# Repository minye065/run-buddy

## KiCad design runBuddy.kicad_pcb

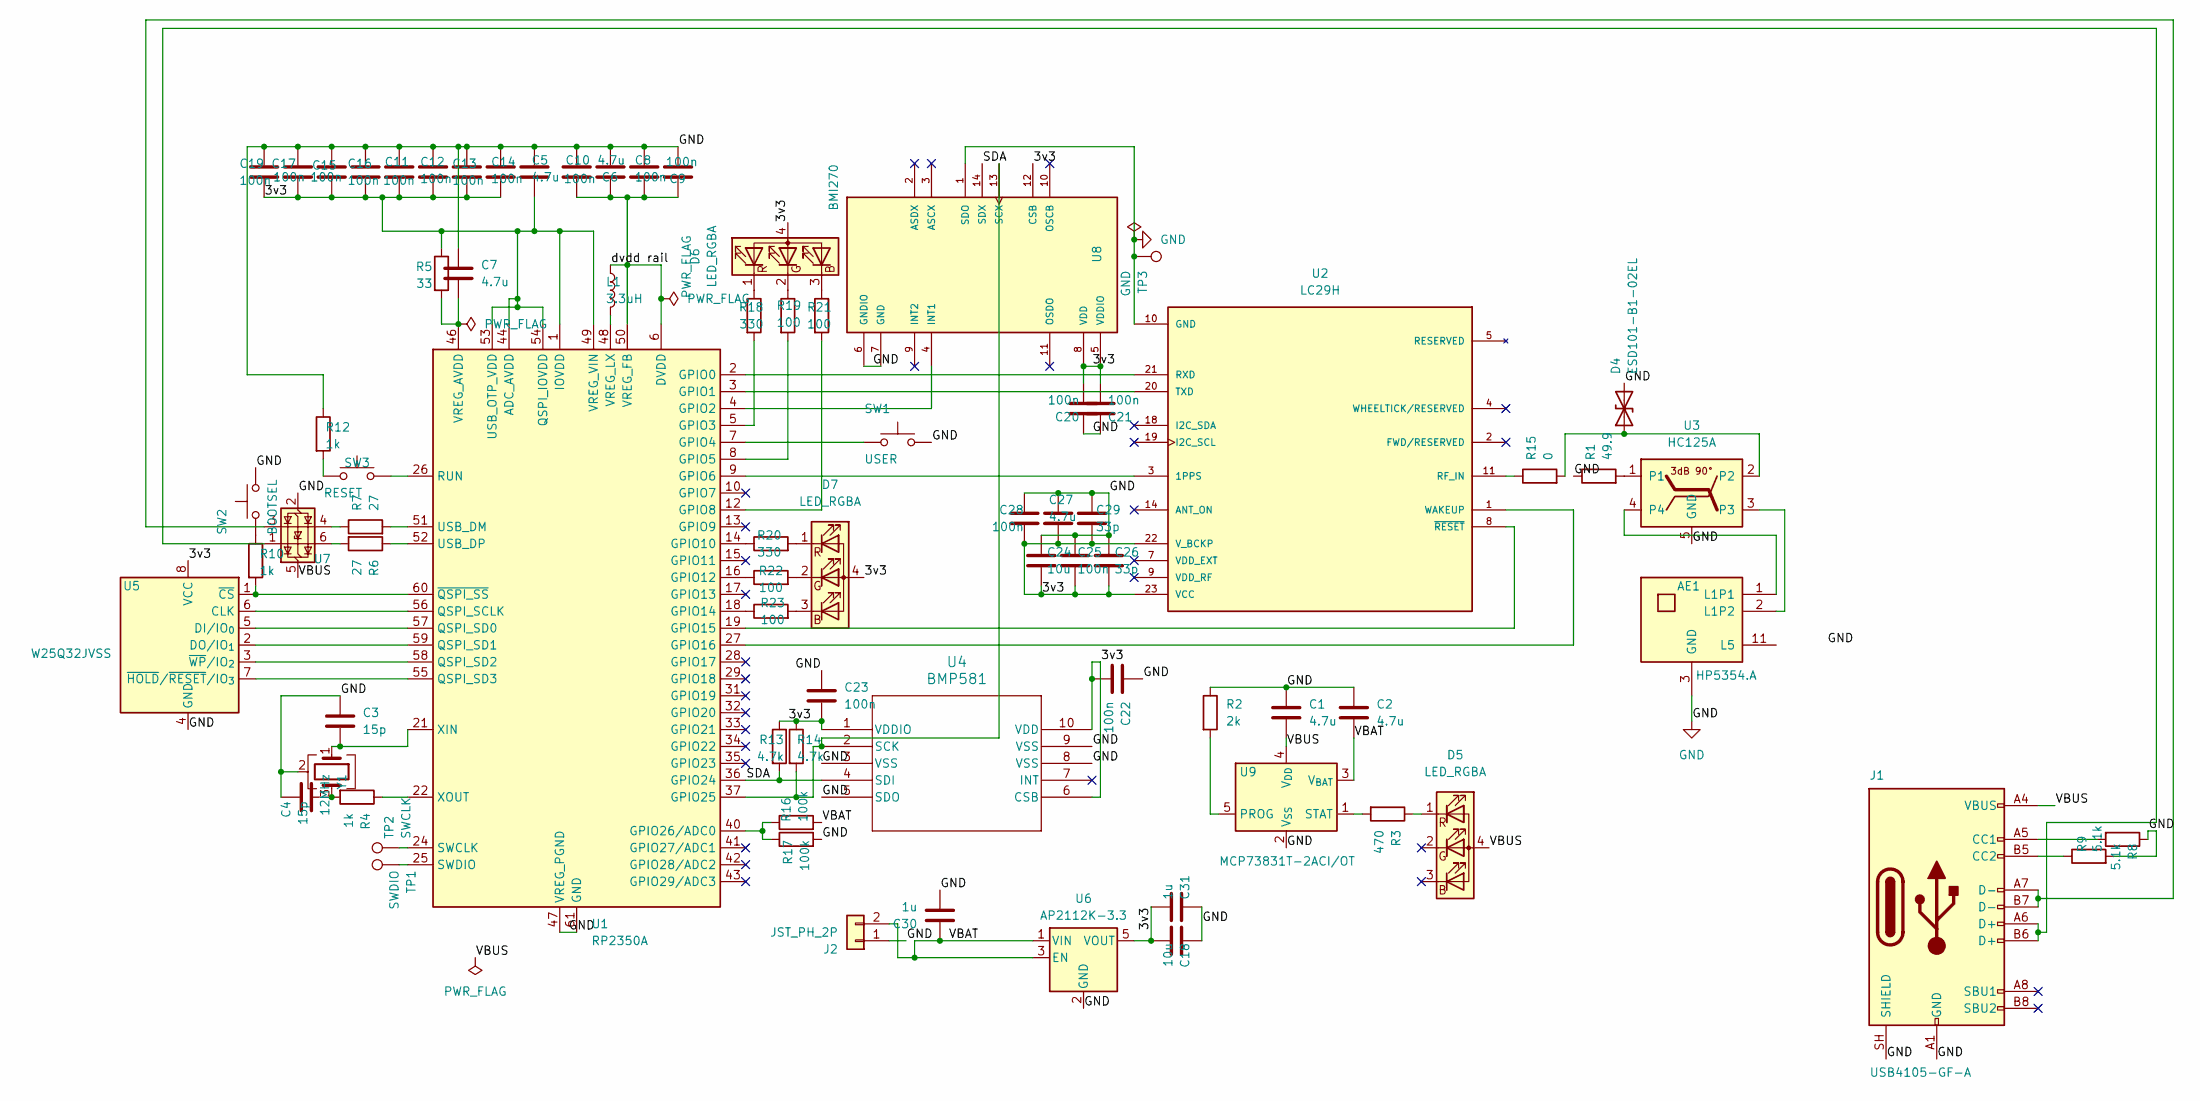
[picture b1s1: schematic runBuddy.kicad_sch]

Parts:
AE1: HP5354.A; MPN HP5354.A
C1, C2, C5, C6, C7, C27: 4.7u; C_0402_1005Metric
C3, C4: 15p; C_0402_1005Metric
C8, C9, C10, C11, C12, C13, C14, C15, C16, C17, C19, C20, C21, C22, C23, C25, C28: 100n; C_0402_1005Metric
C18: 10u; C_0805_2012Metric
C24: 10u; C_0402_1005Metric
C26, C29: 33p; C_0402_1005Metric
C30, C31: 1u; C_0402_1005Metric
D4: ESD101-B1-02EL; D_0201_0603Metric; MPN ESD101-B1-02EL
D5, D6, D7: LED_RGBA; 150066M153000
J1: USB4105-GF-A; USB_C_Receptacle_GCT_USB4105-xx-A_16P_TopMnt_Horizontal; MPN USB4105-GF-A
J2: JST_PH_2P; JST_PH_B2B-PH-K_1x02_P2.00mm_Vertical
L1: 3.3uH; AOTA-B2016; MPN AOTA-B201610S3R3-101-T
R1: 49.9; R_0402_1005Metric; MPN ERJ-2RKF49R9X
R2: 2k; R_0402_1005Metric
R3: 470; R_0402_1005Metric
R4, R10, R12: 1k; R_0402_1005Metric
R5: 33; R_0402_1005Metric
R6, R7: 27; R_0402_1005Metric
R8, R9: 5.1k; R_0402_1005Metric
R13, R14: 4.7k; R_0402_1005Metric
R15: 0; R_0402_1005Metric
R16, R17: 100k; R_0402_1005Metric
R18, R20: 330; R_0402_1005Metric
R19, R21, R22, R23: 100; R_0402_1005Metric
SW1: USER; SW_Push_1P1T_NO_Vertical_Wuerth_434133025816; MPN 434133025816
SW2: BOOTSEL; SW_Push_1P1T_NO_Vertical_Wuerth_434133025816; MPN 434133025816
SW3: RESET; SW_Push_1P1T_NO_Vertical_Wuerth_434133025816; MPN 434133025816
TP1: SWDIO; TestPoint_Pad_D1.0mm
TP2: SWCLK; TestPoint_Pad_D1.0mm
TP3: GND; TestPoint_Pad_D1.0mm
U1: RP2350A; QFN-60-1EP_7x7mm_P0.4mm_EP3.4x3.4mm
U2: LC29H; PARTREV 1.1
U3: HC125A; MPN HC125A
U4: BMP581
U5: W25Q32JVSS; SOIC-8_5.3x5.3mm_P1.27mm
U6: AP2112K-3.3; SOT-23-5
U7: USBLC6-2SC6; SOT-23-6
U8: BMI270
U9: MCP73831T-2ACI/OT; SOT-23-5; MPN MCP73831T-2ACI/OT
Y1: 12MHz; Crystal_SMD_3225-4Pin_3.2x2.5mm; MPN ABM8-272-T3

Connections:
/3v3: C5.2, C11.2, C12.2, C13.2, C14.2, C15.2, C16.2, C17.2, C18.2, C19.2, C20.2, C21.2, C22.2, C23.2, C24.2, C25.2, C26.2, C27.2, C28.2, C29.2, C31.2, D6.4 (A), D7.4 (A), R5.1, R13.1, R14.1, U1.1 (IOVDD), U1.11 (IOVDD), U1.20 (IOVDD), U1.30 (IOVDD), U1.38 (IOVDD), U1.44 (ADC_AVDD), U1.45 (IOVDD), U1.49 (VREG_VIN), U1.53 (USB_OTP_VDD), U1.54 (QSPI_IOVDD), U2.22 (V_BCKP), U2.23 (VCC), U4.1 (VDDIO), U4.6 (CSB), U4.10 (VDD), U5.8 (VCC), U6.5 (VOUT), U8.5 (VDDIO), U8.8 (VDD), U8.12 (CSB)
/SDA: R13.2, U1.36 (GPIO24), U4.4 (SDI), U8.14 (SDX)
/VBAT: C2.2, C30.1, J2.2, R16.2, U6.1 (VIN), U6.3 (EN), U9.3 (V_{BAT})
/VBUS: C1.2, D5.4 (A), J1.A4 (VBUS), J1.A9 (VBUS), J1.B4 (VBUS), J1.B9 (VBUS), U7.5 (VBUS), U9.4 (V_{DD})
/dvdd rail: C6.2, C8.2, C9.1, C10.2, L1.1, U1.6 (DVDD), U1.23 (DVDD), U1.39 (DVDD), U1.50 (VREG_FB)
GND: AE1.3 (GND), AE1.4 (GND), AE1.5 (GND), AE1.6 (GND), AE1.7 (GND), AE1.8 (GND), AE1.9 (GND), AE1.10 (GND), C1.1, C2.1, C3.1, C4.1, C5.1, C6.1, C7.1, C8.1, C9.2, C10.1, C11.1, C12.1, C13.1, C14.1, C15.1, C16.1, C17.1, C18.1, C19.1, C20.1, C21.1, C22.1, C23.1, C24.1, C25.1, C26.1, C27.1, C28.1, C29.1, C30.2, C31.1, D4.2 (A2), J1.A1 (GND), J1.A12 (GND), J1.B1 (GND), J1.B12 (GND), J1.SH (SHIELD), J2.1, R1.1, R2.1, R8.1, R9.2, R12.1, R17.2, SW1.2, SW2.2, TP3.1 (1_1), U1.47 (VREG_PGND), U1.61 (GND), U2.10 (GND), U2.12 (GND), U2.13 (GND), U2.24 (GND), U3.5 (GND), U4.3 (VSS), U4.5 (SDO), U4.8 (VSS), U4.9 (VSS), U5.4 (GND), U6.2 (GND), U7.2 (GND), U8.1 (SDO), U8.6 (GNDIO), U8.7 (GND), U9.2 (V_{SS}), Y1.2 (G), Y1.4 (G)
unnamed: AE1.1 (L1P1), U3.4
unnamed: AE1.2 (L1P2), U3.3
unnamed: C4.2, R4.2, Y1.3
unnamed: D4.1 (A1), R15.2, U3.2
unnamed: D5.1 (RK), R3.1
unnamed: D6.3 (BK), R21.1
unnamed: D6.2 (GK), R19.1
unnamed: D6.1 (RK), R18.1
unnamed: D7.3 (BK), R23.2
unnamed: D7.2 (GK), R22.2
unnamed: D7.1 (RK), R20.2
unnamed: J1.A5 (CC1), R8.2
unnamed: J1.B5 (CC2), R9.1
unnamed: J1.A6 (D+), J1.B6 (D+), U7.1 (I/O1)
unnamed: J1.A7 (D-), J1.B7 (D-), U7.3 (I/O2)
unnamed: R6.2, U7.6 (I/O1)
unnamed: R7.1, U7.4 (I/O2)
unnamed: R10.1, SW2.1
unnamed: R12.2, SW3.1
unnamed: U1.2 (GPIO0), U2.21 (RXD)
unnamed: U1.3 (GPIO1), U2.20 (TXD)
unnamed: U1.4 (GPIO2), U8.4 (INT1)
unnamed: R18.2, U1.5 (GPIO3)
unnamed: SW1.1, U1.7 (GPIO4)
unnamed: R19.2, U1.8 (GPIO5)
unnamed: U1.9 (GPIO6), U2.3 (1PPS)
unnamed: R21.2, U1.12 (GPIO8)
unnamed: R20.1, U1.14 (GPIO10)
unnamed: R22.1, U1.16 (GPIO12)
unnamed: R23.1, U1.18 (GPIO14)
unnamed: U1.19 (GPIO15), U2.8 (~RESET)
unnamed: U1.27 (GPIO16), U2.1 (WAKEUP)
unnamed: R14.2, U1.37 (GPIO25), U4.2 (SCK), U8.13 (SCX)
unnamed: R16.1, R17.1, U1.40 (GPIO26/ADC0)
unnamed: U1.56 (QSPI_SCLK), U5.6 (CLK)
unnamed: U1.57 (QSPI_SD0), U5.5 (DI/IO_{0})
unnamed: U1.59 (QSPI_SD1), U5.2 (DO/IO_{1})
unnamed: U1.58 (QSPI_SD2), U5.3 (~WP/IO_{2})
unnamed: U1.55 (QSPI_SD3), U5.7 (~HOLD/~RESET/IO_{3})
unnamed: SW3.2, U1.26 (RUN)
unnamed: TP2.1 (1_1), U1.24 (SWCLK)
unnamed: TP1.1 (1_1), U1.25 (SWDIO)
unnamed: R7.2, U1.51 (USB_DM)
unnamed: R6.1, U1.52 (USB_DP)
unnamed: C7.2, R5.2, U1.46 (VREG_AVDD)
unnamed: L1.2, U1.48 (VREG_LX)
unnamed: C3.2, U1.21 (XIN), Y1.1
unnamed: R4.1, U1.22 (XOUT)
unnamed: R10.2, U1.60 (~QSPI_SS), U5.1 (~CS)
unnamed: R15.1, U2.11 (RF_IN)
unnamed: R1.2, U3.1
unnamed: R2.2, U9.5 (PROG)
unnamed: R3.2, U9.1 (STAT)

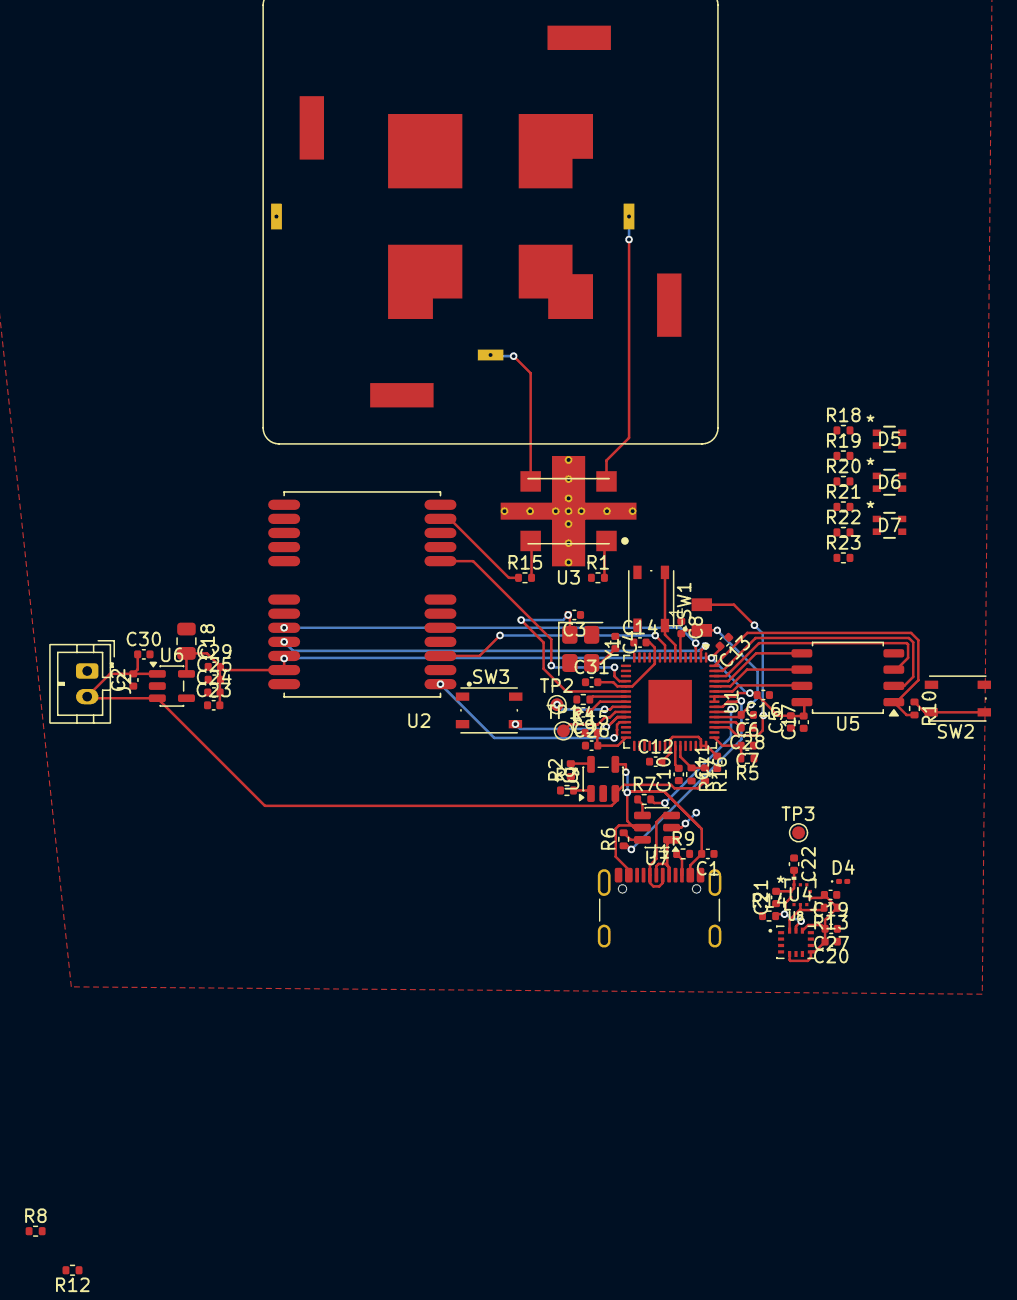
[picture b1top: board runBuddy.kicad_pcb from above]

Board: 2 copper layers, 77 parts (0 on the bottom side), 59 nets.
